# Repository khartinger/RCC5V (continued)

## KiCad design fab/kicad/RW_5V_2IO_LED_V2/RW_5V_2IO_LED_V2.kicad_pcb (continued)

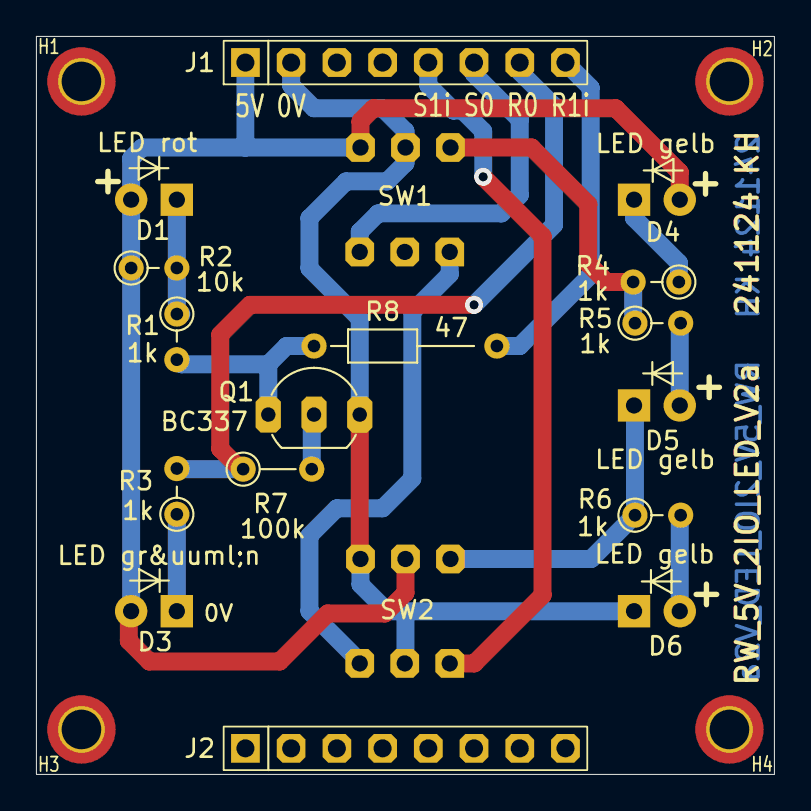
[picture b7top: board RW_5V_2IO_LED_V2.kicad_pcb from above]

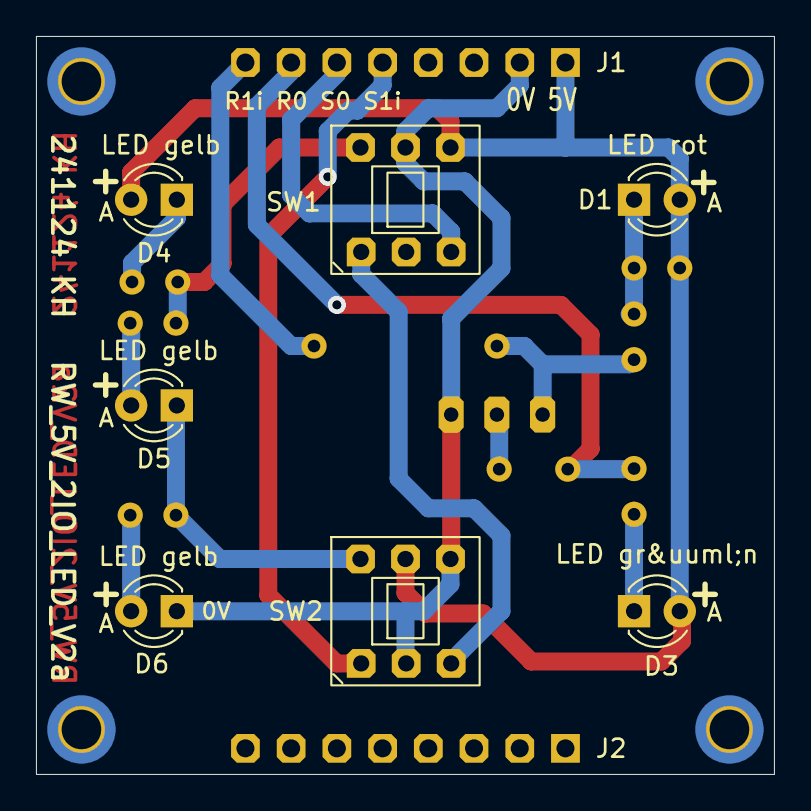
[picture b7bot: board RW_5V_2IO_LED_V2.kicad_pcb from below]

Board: 2 copper layers, 41.0 x 41.0 mm, 22 parts (7 on the bottom side), 16 nets.
